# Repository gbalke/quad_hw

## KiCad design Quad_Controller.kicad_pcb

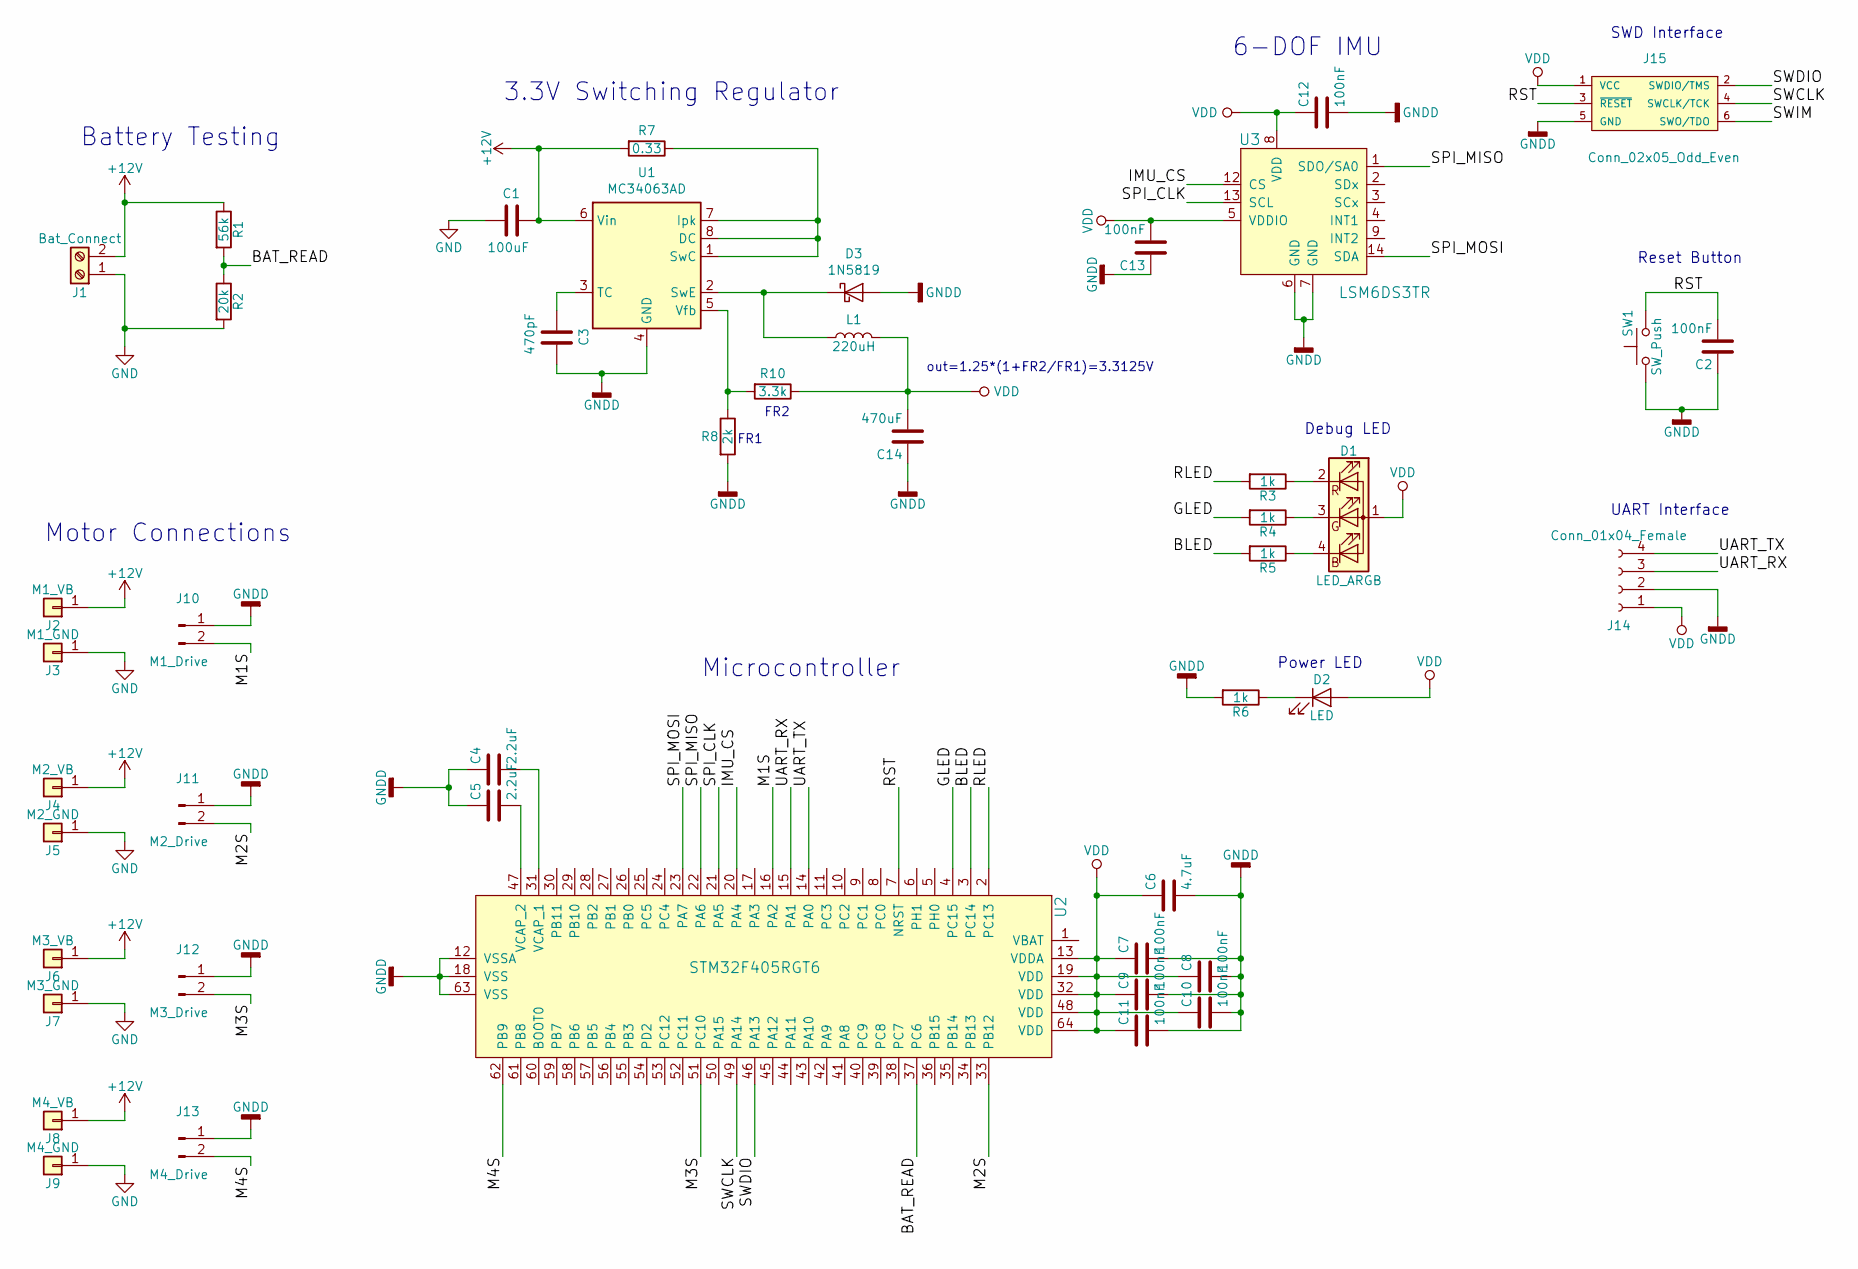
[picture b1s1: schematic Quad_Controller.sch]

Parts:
C1: 100uF; CP_Elec_5x5.3
C2, C7, C8, C9, C10, C11, C12, C13: 100nF; C_0603_1608Metric
C3: 470pF; C_0603_1608Metric
C4, C5: 2.2uF; C_0603_1608Metric
C6: 4.7uF; C_0603_1608Metric
C14: 470uF; C_0603_1608Metric
D1: LED_ARGB; LED_RGB_1210
D2: LED; LED_0603_1608Metric
D3: 1N5819; D_DO-41_SOD81_P10.16mm_Horizontal
J1: Bat_Connect; TerminalBlock_bornier-2_P5.08mm
J2: M1_VB; SolderWirePad_single_SMD_3x6mm
J3: M1_GND; SolderWirePad_single_SMD_3x6mm
J4: M2_VB; SolderWirePad_single_SMD_3x6mm
J5: M2_GND; SolderWirePad_single_SMD_3x6mm
J6: M3_VB; SolderWirePad_single_SMD_3x6mm
J7: M3_GND; SolderWirePad_single_SMD_3x6mm
J8: M4_VB; SolderWirePad_single_SMD_3x6mm
J9: M4_GND; SolderWirePad_single_SMD_3x6mm
J10: M1_Drive; Molex_PicoBlade_53047-0210_1x02_P1.25mm_Vertical
J11: M2_Drive; Molex_PicoBlade_53047-0210_1x02_P1.25mm_Vertical
J12: M3_Drive; Molex_PicoBlade_53047-0210_1x02_P1.25mm_Vertical
J13: M4_Drive; Molex_PicoBlade_53047-0210_1x02_P1.25mm_Vertical
J14: Conn_01x04_Female; Molex_PicoBlade_53047-0410_1x04_P1.25mm_Vertical
J15: Conn_02x05_Odd_Even; TC2030-NL_SMALL
L1: 220uH; L_Bourns_SRN6045TA
R1: 56k; R_0603_1608Metric
R2: 20k; R_0603_1608Metric
R3, R4, R5, R6: 1k; R_0603_1608Metric
R7: 0.33; R_0805_2012Metric
R8: 2k; R_0603_1608Metric
R10: 3.3k; R_0603_1608Metric
SW1: SW_Push; SW_SPST_B3U-1000P
U1: MC34063AD; SOIC-8_3.9x4.9mm_P1.27mm
U2: STM32F405RGT6; LQFP-64_10x10mm; MPN STM32F405RGT6; Digi-Key_PN 497-11767-ND
U3: LSM6DS3TR; LGA-14L_2.5x3mm__LSM6DS3; MPN LSM6DS3TR; Digi-Key_PN 497-15383-1-ND

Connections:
+12V: C1.2, J1.2, J2.1, J4.1, J6.1, J8.1, R1.1, R7.2, U1.6 (Vin)
/BAT_READ: R1.2, R2.1, U2.37 (PC6)
/BLED: R5.2, U2.3 (PC14)
/GLED: R4.2, U2.4 (PC15)
/IMU_CS: U2.20 (PA4), U3.12 (CS)
/M1S: J10.2, U2.16 (PA2)
/M2S: J11.2, U2.33 (PB12)
/M3S: J12.2, U2.51 (PC10)
/M4S: J13.2, U2.62 (PB9)
/RLED: R3.2, U2.2 (PC13)
/RST: C2.2, J15.3 (~RESET~), SW1.2, U2.7 (NRST)
/SPI_CLK: U2.21 (PA5), U3.13 (SCL)
/SPI_MISO: U2.22 (PA6), U3.1 (SDO/SA0)
/SPI_MOSI: U2.23 (PA7), U3.14 (SDA)
/SWCLK: J15.4 (SWCLK/TCK), U2.49 (PA14)
/SWDIO: J15.2 (SWDIO/TMS), U2.46 (PA13)
/SWIM: J15.6 (SWO/TDO)
/UART_RX: J14.3, U2.15 (PA1)
/UART_TX: J14.4, U2.14 (PA0)
GND: C1.1, J1.1, J3.1, J5.1, J7.1, J9.1, R2.2
GNDD: C2.1, C3.2, C4.1, C5.1, C6.2, C7.2, C8.2, C9.2, C10.2, C11.2, C12.2, C13.1, C14.1, D3.2 (A), J10.1, J11.1, J12.1, J13.1, J14.2, J15.5 (GND), R6.2, R8.2, SW1.1, U1.4 (GND), U2.12 (VSSA), U2.18 (VSS), U2.63 (VSS), U3.6 (GND), U3.7 (GND)
unnamed: C3.1, U1.3 (TC)
unnamed: C4.2, U2.31 (VCAP_1)
unnamed: C5.2, U2.47 (VCAP_2)
unnamed: D1.2 (RK), R3.1
unnamed: D1.3 (GK), R4.1
unnamed: D1.4 (BK), R5.1
unnamed: D2.1 (K), R6.1
unnamed: D3.1 (K), L1.1, U1.2 (SwE)
unnamed: R7.1, U1.1 (SwC), U1.7 (Ipk), U1.8 (DC)
unnamed: R8.1, R10.2, U1.5 (Vfb)
VDD: C6.1, C7.1, C8.1, C9.1, C10.1, C11.1, C12.1, C13.2, C14.2, D1.1 (A), D2.2 (A), J14.1, J15.1 (VCC), L1.2, R10.1, U2.13 (VDDA), U2.19 (VDD), U2.32 (VDD), U2.48 (VDD), U2.64 (VDD), U3.5 (VDDIO), U3.8 (VDD)

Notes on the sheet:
Microcontroller
Battery Testing
6-DOF IMU
SWD Interface
3.3V Switching Regulator
Reset Button
Debug LED
UART Interface
Power LED
Motor Connections
out=1.25*(1+FR2/FR1)=3.3125V
FR1
FR2

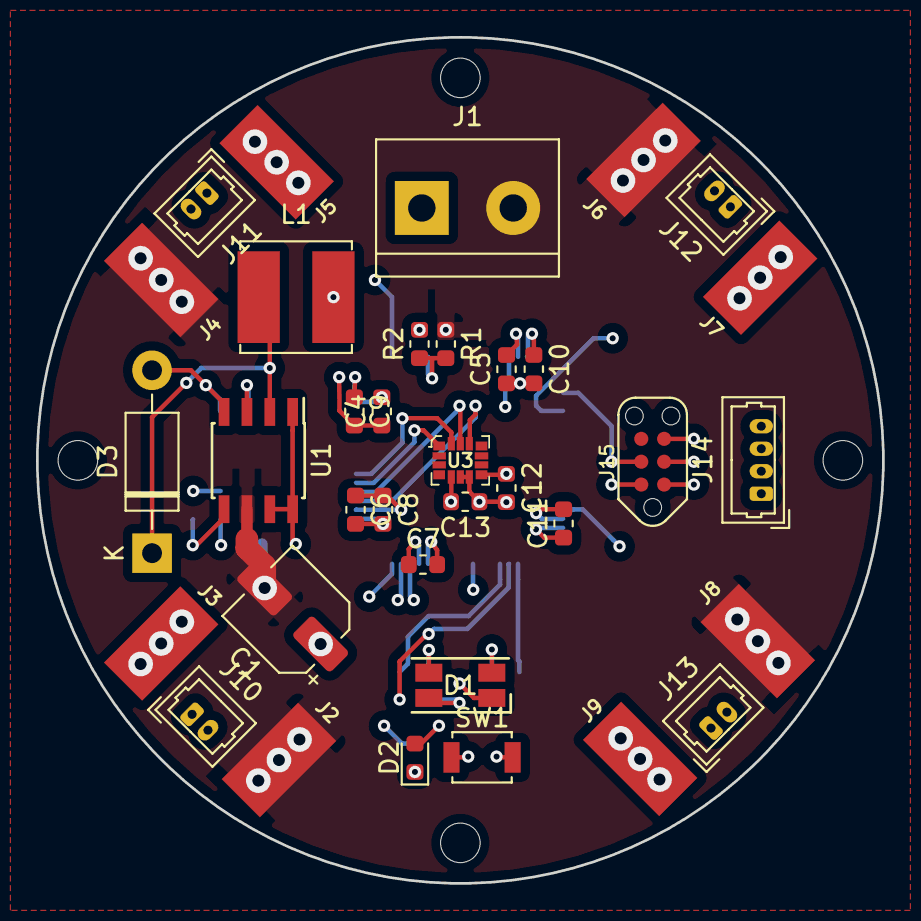
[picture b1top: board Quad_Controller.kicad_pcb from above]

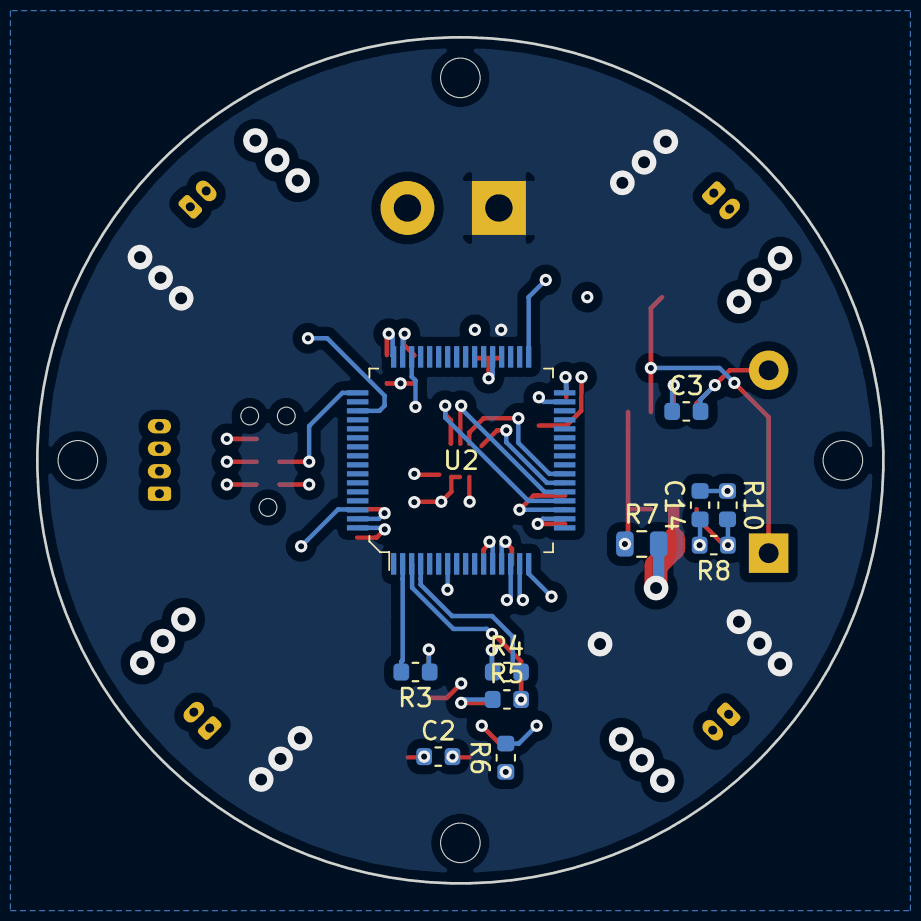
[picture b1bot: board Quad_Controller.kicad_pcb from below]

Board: 4 copper layers, 47.0 x 47.0 mm, 46 parts (11 on the bottom side), 31 nets.

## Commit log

2019-04-11 Moving local copy to github
2019-04-26 Major overhaul to fix schematic after transition to new library format
2019-04-26 Fixing dumb mistake Capacitors -> Capacitor (same with resistor)
2019-05-20 Adding some small updates (redoing layout with components on back of board)
2019-05-25 Finished re-routing new design
2019-07-15 Connecting missed pad and clarifying formula for output of switching regulator)
